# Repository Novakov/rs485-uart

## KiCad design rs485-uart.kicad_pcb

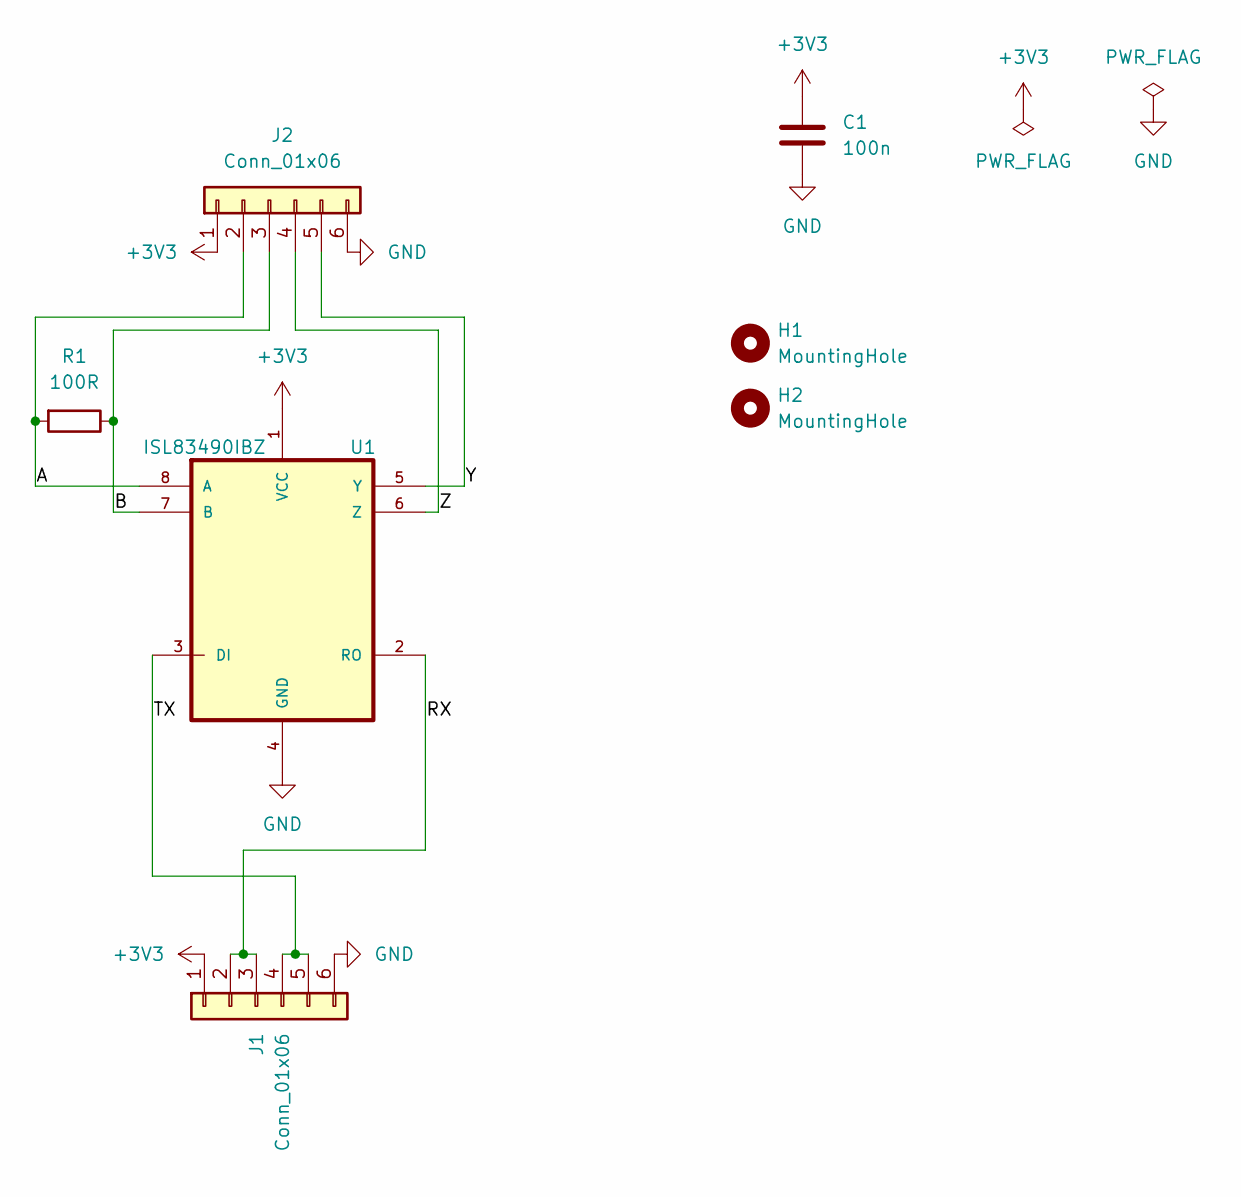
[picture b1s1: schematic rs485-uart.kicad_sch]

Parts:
C1: 100n; C_0603_1608Metric_Pad1.08x0.95mm_HandSolder
H1, H2: MountingHole; MountingHole_3.2mm_M3
J1: Conn_01x06; PinSocket_1x06_P2.54mm_Horizontal
J2: Conn_01x06; PinHeader_1x06_P2.54mm_Horizontal
R1: 100R; R_0603_1608Metric_Pad0.98x0.95mm_HandSolder
U1: ISL83490IBZ; SOIC-8_3.9x4.9mm_P1.27mm

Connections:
+3V3: C1.1, J1.1, J2.1, U1.1 (VCC)
/A: J2.2, R1.2, U1.8 (A)
/B: J2.3, R1.1, U1.7 (B)
/RX: J1.2, J1.3, U1.2 (RO)
/TX: J1.4, J1.5, U1.3 (DI)
/Y: J2.5, U1.5 (Y)
/Z: J2.4, U1.6 (Z)
GND: C1.2, J1.6, J2.6, U1.4 (GND)

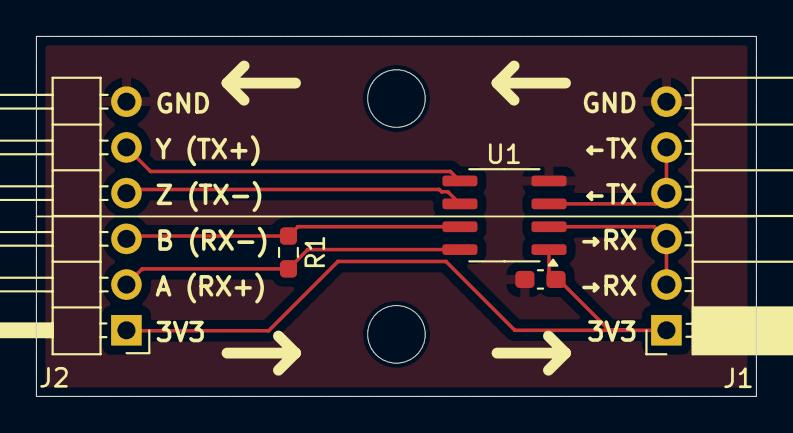
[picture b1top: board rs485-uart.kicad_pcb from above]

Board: 2 copper layers, 40.0 x 20.0 mm, 7 parts (0 on the bottom side), 8 nets.

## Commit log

2024-07-31 Tuning
